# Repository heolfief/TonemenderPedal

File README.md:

# Tonemender by runoffgroove.com

Original design here : [runoffgroove.com/tonemender.html](http://runoffgroove.com/tonemender.html)

The Tonemender is a very flexible, yet simple clean boost with a 3-knob tonestack that allows the user to re-create the classic Fender, Marshall and Vox responses.

Gerbers can be found in the Hardware folder.

This repository shares an SMD version of the pedal's PCB. This is the original design, only the PCB layout changed <br> to make it smaller and easier to fit in small pedal's enclosures. 

### Listen to it : 
- [Clean](http://runoffgroove.com/tmclean.mp3)
- [Fuzz](http://runoffgroove.com/tmfuzz.mp3)

> Both clips follow the order of bypassed, then Fender, Marshall, Vox modes. For Clip 2, the Sili-Face was placed before the Tonemender and both pickups were on.

### License :
 Tonemender by runoffgroove.com is licensed under a [Creative Commons Attribution-NonCommercial-ShareAlike 3.0 Unported License](https://creativecommons.org/licenses/by-nc-sa/3.0/).

<hr>
PCBWAYS offers non-profit engineering projects sponsorship for students : https://www.pcbway.com/project/sponsor/

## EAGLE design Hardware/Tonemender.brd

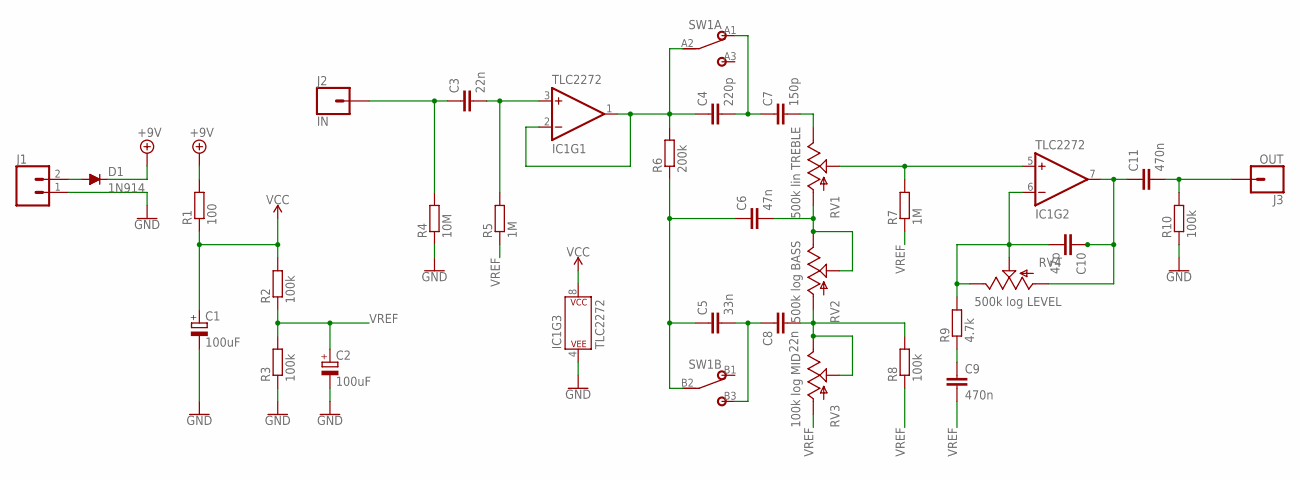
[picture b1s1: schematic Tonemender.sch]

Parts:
C1, C2: 100uF; E2,5-5
C3, C8: 22n; C0805
C4: 220p; C0805
C5: 33n; C0805
C6: 47n; C0805
C7: 150p; C0805
C9, C11: 470n; C0805
C10: 47p; C0805
D1: 1N914; DO35-6
IC1: TLC2272; SO08
J1: CONN_02; 1X02
J2: IN; 1X01
J3: OUT; 1X01
R1: 100; M0805
R2, R3, R8, R10: 100k; M0805
R4: 10M; M0805
R5, R7: 1M; M0805
R6: 200k; M0805
R9: 4.7k; M0805
RV1: 500k lin TREBLE; 1X03
RV2: 500k log BASS; 1X03
RV3: 100k log MID; 1X03
RV4: 500k log LEVEL; 1X03
SW1: DPDTPADS; DPDT_PADS

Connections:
+9V: D1.C, R1.2
GND: C1.-, C2.-, IC1.4 (P$V-), J1.1, R3.1, R4.1, R10.1
unnamed: C4.1, IC1.1 (OUT), IC1.2 (-IN), R6.2, SW1.A2 (2)
unnamed: C3.2, IC1.3 (+IN), R5.2
unnamed: C4.2, C7.1, SW1.A1 (1)
unnamed: C7.2, RV1.3 (E)
unnamed: C5.1, C6.1, R6.1, SW1.B2 (2)
unnamed: C6.2, RV1.1 (A), RV2.2 (S), RV2.3 (E)
unnamed: C5.2, C8.1, SW1.B3 (3)
unnamed: C8.2, R8.2, RV2.1 (A), RV3.2 (S), RV3.3 (E)
unnamed: IC1.5 (+IN), R7.2, RV1.2 (S)
unnamed: C10.1, C11.1, IC1.7 (OUT), RV4.1 (A)
unnamed: C10.2, IC1.6 (-IN), R9.2, RV4.2 (S), RV4.3 (E)
unnamed: D1.A, J1.2
unnamed: C9.1, R9.1
unnamed: C3.1, J2.1, R4.2
unnamed: C11.2, J3.1, R10.2
VCC: C1.+, IC1.8 (P$V+), R1.1, R2.2
VREF: C2.+, C9.2, R2.1, R3.2, R5.1, R7.1, R8.1, RV3.1 (A)

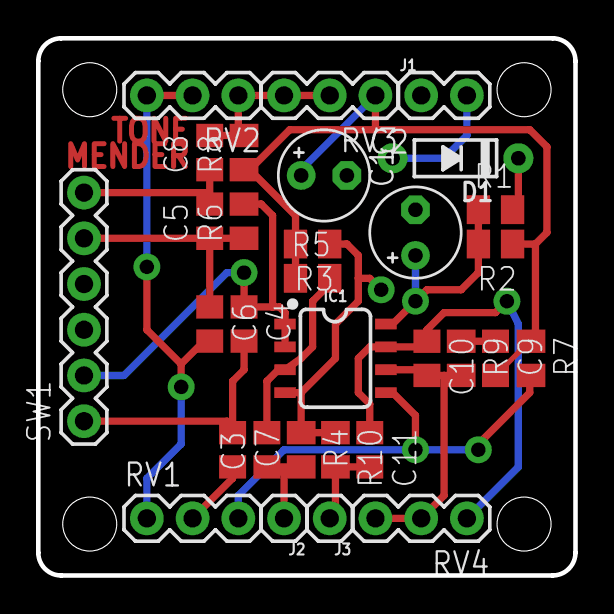
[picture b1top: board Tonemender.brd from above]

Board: 2 copper layers, 29.8 x 29.8 mm, 31 parts (0 on the bottom side), 19 nets.

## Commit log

2018-01-28 Add files
2018-01-28 Add PCB 3D render
2018-11-06 [ImgBot] Optimize images
    *Total -- 1,621.94kb -> 1,559.16kb (3.87%)
    /Resources/full.jpg -- 290.65kb -> 274.79kb (5.46%)
    /Resources/front.jpg -- 620.85kb -> 589.61kb (5.03%)
    /Resources/inside.jpg -- 555.24kb -> 539.60kb (2.82%)
    /Resources/PCB 3D render.jpg -- 155.20kb -> 155.16kb (0.03%)
2020-10-27 Add gerbers
2020-10-27 Add gerber info

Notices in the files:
parts and their libraries:
SparkFun-IC-Amplifiers: Licensing: Creative Commons ShareAlike 4.0 International - https://creativecommons.org/licenses/by-sa/4.0
